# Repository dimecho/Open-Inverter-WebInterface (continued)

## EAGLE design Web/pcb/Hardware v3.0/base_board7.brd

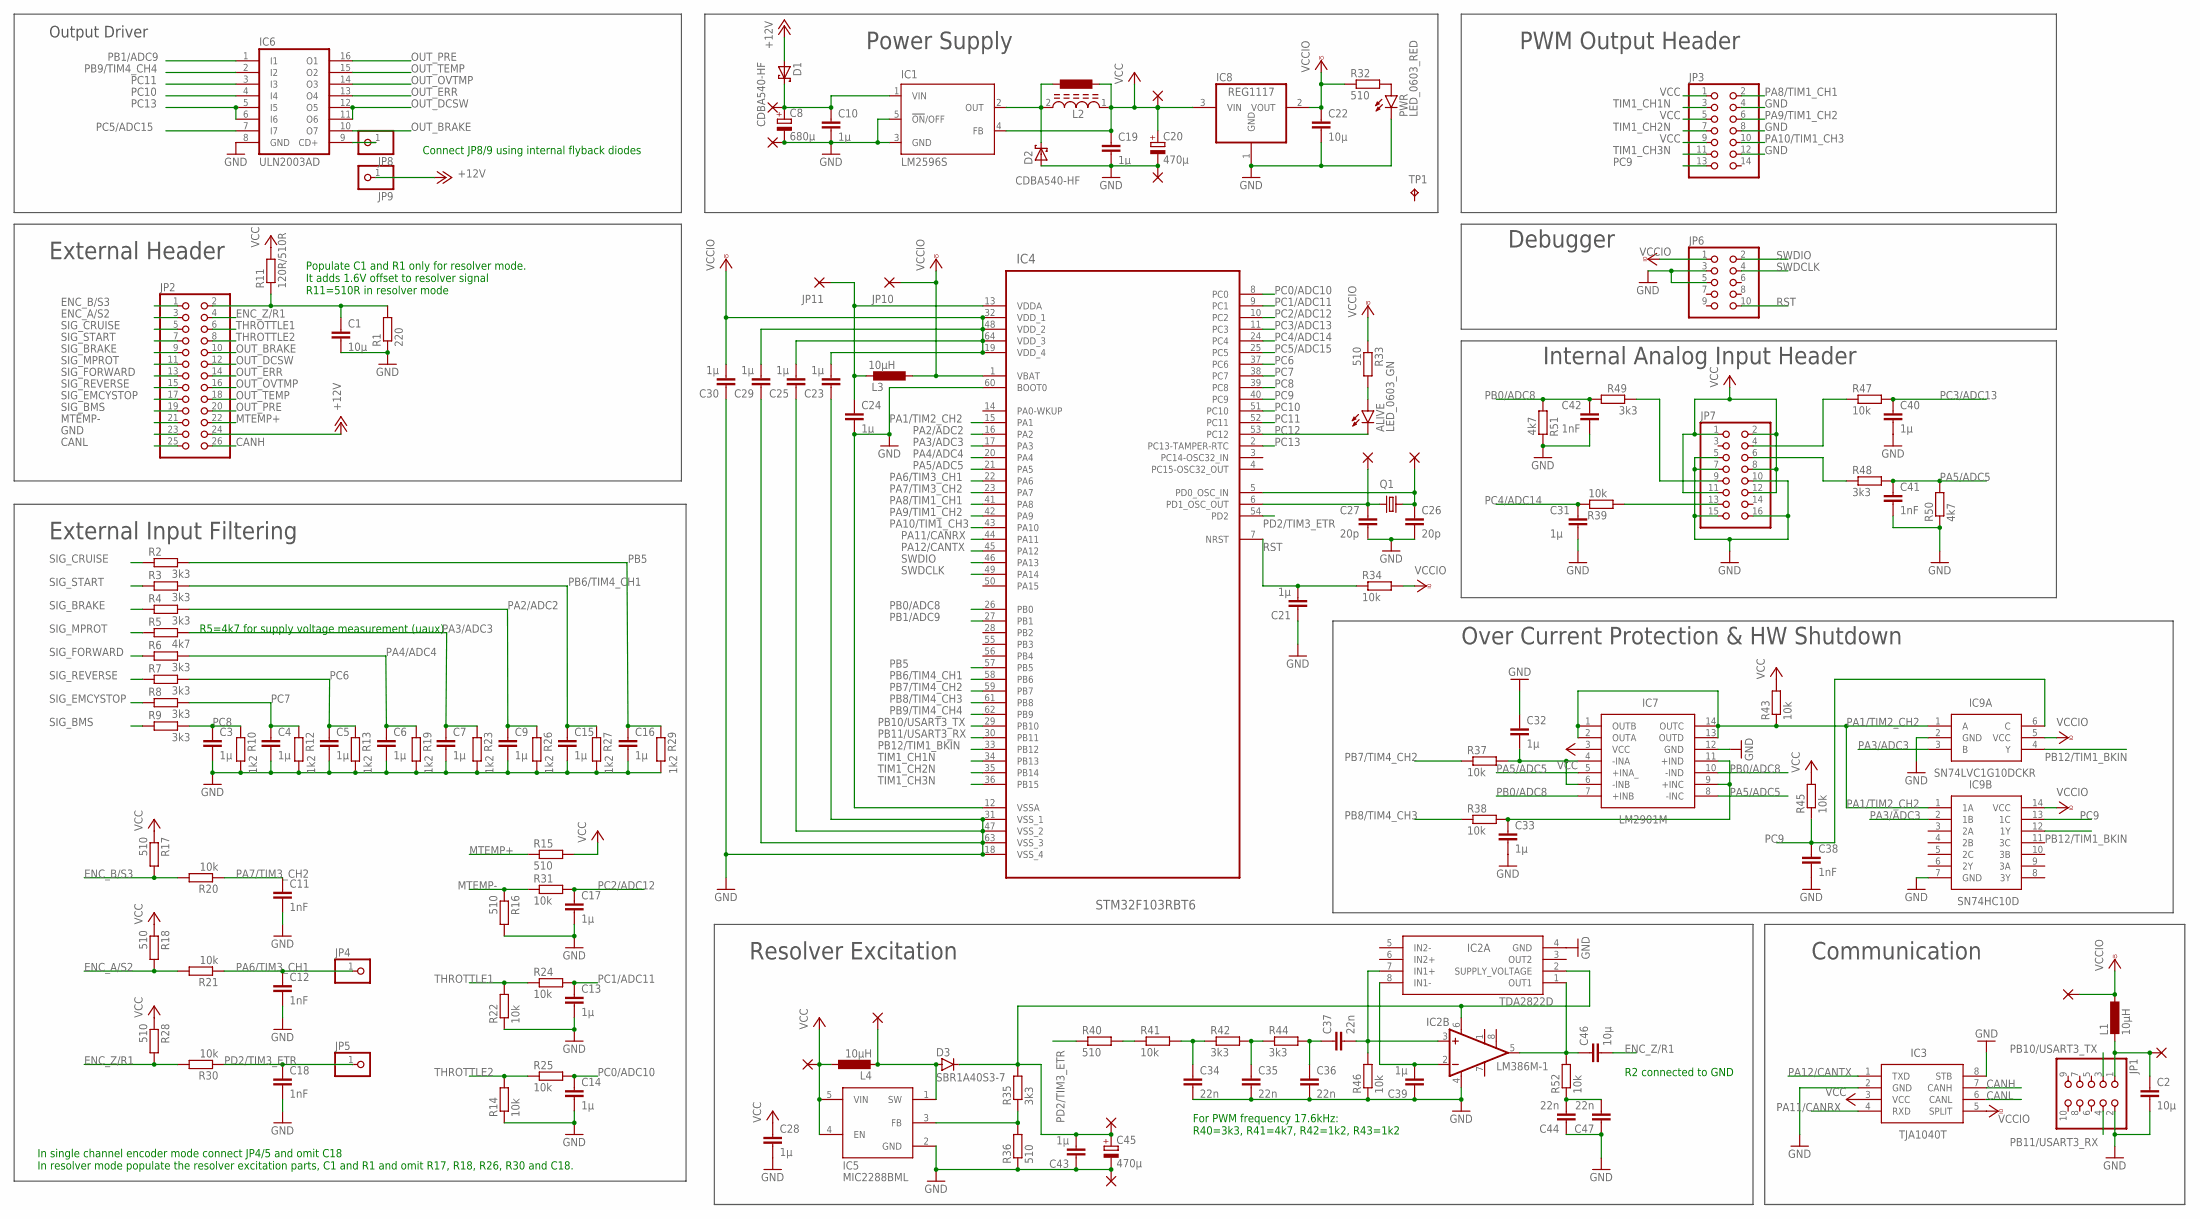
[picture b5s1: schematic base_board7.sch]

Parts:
ALIVE: LED_0603_GN; SML0805
C1, C2, C22, C46: 10µ; C0805K
C3, C4, C5, C6, C7, C9, C10, C13, C14, C15, C16, C17, C19, C21, C23, C24, C25, C28, C29, C30, C31, C32, C33, C39, C40, C43: 1µ; C0603K
C8: 680µ; 153CLV-1014
C11, C12, C18, C38, C41, C42: 1nF; C0603K
C20, C45: 470µ; 153CLV-0605
C26, C27: 20p; C0603K
C34, C35, C36, C37, C44, C47: 22n; C0603K
D1, D2: CDBA540-HF; SMB
D3: SBR1A40S3-7; SOD123
IC1: LM2596S; TO263-5
IC2A: TDA2822D; SOIC127P600X175-8N
IC2B: LM386M-1; SO08
IC3: TJA1040T; SOIC127P600X175-8N
IC4: STM32F103RBT6; QFP50P1200X1200X160-64N
IC5: MIC2288BML; SOT23-5L
IC6: ULN2003AD; SO16
IC7: LM2901M; SOP127P600X180-14N
IC8: REG1117; SOT223
IC9A: SN74LVC1G10DCKR; SOT65P210X110-6N
IC9B: SN74HC10D; SOIC127P600X175-14N
JP1: PINHD-2X5/90; 2X05/90
JP2: PINHD-2X13; 2X13
JP3: PINHD-2X7; 2X07
JP4, JP5, JP8, JP9: PINHD-1X1; 1X01
JP6: PINHD-2X5; 2X05
JP7: PINHD-2X8; 2X08
JP10, JP11: 1,6/0,9
JP12, JP13, JP14, JP15, JP16, JP17: 1,6/0,8
L1, L3, L4: 10µH; L3225M
L2: SRR1260-471K; INDP125125X600N
L5: L-EUTJ3-U1; TJ3-U1
PAD1, PAD2: 1,6/0,9
PAD3, PAD4, PAD5, PAD6: 1,6/0,8
PWR: LED_0603_RED; SML0805
Q1: CSM-7X-DU
R1: 220; R0603
R2, R3, R4, R6, R7, R8, R9, R35, R42, R44, R48, R49: 3k3; R0603
R5, R50, R51: 4k7; R0603
R10, R12, R13, R19, R23, R26, R27, R29: 1k2; R0603
R11: 120R/510R; R0603
R14, R20, R21, R22, R24, R25, R30, R31, R34, R37, R38, R39, R41, R43, R45, R46, R47, R52: 10k; R0603
R15, R16, R17, R18, R28, R32, R33, R36, R40: 510; R0603
TP1: TPB1,27; B1,27

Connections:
+12V: D1.A, JP2.24, JP9.1
CANH: IC3.7 (CANH), JP2.26
CANL: IC3.6 (CANL), JP2.25
ENC_A/S2: JP2.3, R18.2, R21.2
ENC_B/S3: JP2.1, R17.2, R20.2
ENC_Z/R1: C46.2, JP2.4, R28.2, R30.2
GND: C1.2, C2.2, C3.2, C4.2, C5.2, C6.2, C7.2, C8.-, C9.2, C10.2, C11.2, C12.2, C13.2, C14.2, C15.2, C16.2, C17.2, C18.2, C19.2, C20.-, C21.1, C22.2, C23.1, C24.2, C25.1, C26.2, C27.2, C28.2, C29.1, C30.1, C31.2, C32.1, C33.2, C34.2, C35.2, C36.2, C38.2, C39.1, C40.2, C41.2, C42.2, C43.1, C44.1, C45.-, C47.1, D2.A, IC1.3 (GND), IC1.5 (!ON!/OFF), IC2A.4 (GND), IC2B.4 (GND), IC3.2 (GND), IC3.8 (STB), IC4.12 (VSSA), IC4.18 (VSS_4), IC4.31 (VSS_1), IC4.47 (VSS_2), IC4.60 (BOOT0), IC4.63 (VSS_3), IC5.2 (GND), IC6.8 (GND), IC7.12 (GND), IC8.1 (GND), IC9A.2 (GND), IC9B.7 (GND), JP1.2, JP2.23, JP3.4, JP3.8, JP3.12, JP6.3, JP6.5, JP7.5, JP7.7, JP7.10, JP7.15, JP7.16, PAD1.1, PAD3.1, PAD6.1, PWR.C, R1.1, R10.2, R12.2, R13.2, R14.1, R16.2, R19.2, R22.1, R23.2, R26.2, R27.2, R29.2, R36.1, R46.1, R50.1, R51.2
MTEMP+: JP2.22, R15.1
MTEMP-: JP2.21, R16.1, R31.1
unnamed: C1.1, JP2.2, R1.2, R11.1
unnamed: ALIVE.A, R33.2
unnamed: D2.C, IC1.2 (OUT), L2.2, L5.1
unnamed: C8.+, C10.1, D1.C, IC1.1 (VIN), PAD2.1
unnamed: PWR.A, R32.2
unnamed: C27.1, IC4.6 (PD1_OSC_OUT), JP17.1, Q1.1
unnamed: C24.1, IC4.13 (VDDA), JP11.1, L3.1
unnamed: IC6.9 (CD+), JP8.1
unnamed: JP7.9, R49.2
unnamed: JP7.13, R39.1
unnamed: JP7.4, R47.1
unnamed: JP7.6, R48.1
unnamed: C32.2, IC7.4 (-INA), IC7.6 (-INB), R37.2
unnamed: C33.1, IC7.9 (+INC), IC7.11 (+IND), R38.2
unnamed: D3.2 (A), IC5.1 (SW), JP13.1, L4.2
unnamed: IC5.3 (FB), R35.1, R36.2
unnamed: C43.2, C45.+, D3.1 (C), IC2A.2 (SUPPLY_VOLTAGE), IC2B.6 (VS), PAD5.1, R35.2
unnamed: R40.2, R41.1
unnamed: C34.1, R41.2, R42.1
unnamed: C35.1, R42.2, R44.1
unnamed: C36.1, C37.1, R44.2
unnamed: C39.2, IC2A.8 (IN1-), IC2B.2 (-IN)
unnamed: C37.2, IC2A.7 (IN1+), IC2B.3 (+IN), R46.2
unnamed: C44.2, C47.2, R52.1
unnamed: C46.1, IC2A.1 (OUT1), IC2B.5 (OUT), R52.2
unnamed: C2.1, JP1.1, JP15.1, L1.2
unnamed: C26.1, IC4.5 (PD0_OSC_IN), JP16.1, Q1.2
OUT_BRAKE: IC6.10 (O7), JP2.10
OUT_DCSW: IC6.11 (O6), IC6.12 (O5), JP2.12
OUT_ERR: IC6.13 (O4), JP2.14
OUT_OVTMP: IC6.14 (O3), JP2.16
OUT_PRE: IC6.16 (O1), JP2.20
OUT_TEMP: IC6.15 (O2), JP2.18
PA1/TIM2_CH2: IC4.15 (PA1), IC7.1 (OUTB), IC7.2 (OUTA), IC7.13 (OUTD), IC7.14 (OUTC), IC9A.1 (A), IC9B.1 (1A), R43.1
PA2/ADC2: C9.1, IC4.16 (PA2), R4.2, R26.1
PA3/ADC3: C7.1, IC4.17 (PA3), IC9A.3 (B), IC9B.2 (1B), R5.2, R23.1
PA4/ADC4: C6.1, IC4.20 (PA4), R6.2, R19.1
PA5/ADC5: C41.1, IC4.21 (PA5), IC7.5 (+INA_), IC7.8 (-INC), R48.2, R50.2
PA6/TIM3_CH1: C12.1, IC4.22 (PA6), JP4.1, R21.1
PA7/TIM3_CH2: C11.1, IC4.23 (PA7), R20.1
PA8/TIM1_CH1: IC4.41 (PA8), JP3.2
PA9/TIM1_CH2: IC4.42 (PA9), JP3.6
PA10/TIM1_CH3: IC4.43 (PA10), JP3.10
PA11/CANRX: IC3.4 (RXD), IC4.44 (PA11)
PA12/CANTX: IC3.1 (TXD), IC4.45 (PA12)
PB0/ADC8: C42.1, IC4.26 (PB0), IC7.7 (+INB), IC7.10 (-IND), R49.1, R51.1
PB1/ADC9: IC4.27 (PB1), IC6.1 (I1)
PB5: C16.1, IC4.57 (PB5), R2.2, R29.1
PB6/TIM4_CH1: C15.1, IC4.58 (PB6), R3.2, R27.1
PB7/TIM4_CH2: IC4.59 (PB7), R37.1
PB8/TIM4_CH3: IC4.61 (PB8), R38.1
PB9/TIM4_CH4: IC4.62 (PB9), IC6.2 (I2)
PB10/USART3_TX: IC4.29 (PB10), JP1.3
PB11/USART3_RX: IC4.30 (PB11), JP1.4
PB12/TIM1_BKIN: IC4.33 (PB12), IC9A.4 (Y), IC9B.12 (1Y)
PC0/ADC10: C14.1, IC4.8 (PC0), R25.2
PC1/ADC11: C13.1, IC4.9 (PC1), R24.2
PC2/ADC12: C17.1, IC4.10 (PC2), R31.2
PC3/ADC13: C40.1, IC4.11 (PC3), R47.2
PC4/ADC14: C31.1, IC4.24 (PC4), R39.2
PC5/ADC15: IC4.25 (PC5), IC6.7 (I7)
PC6: C5.1, IC4.37 (PC6), R7.2, R13.1
PC7: C4.1, IC4.38 (PC7), R8.2, R12.1
PC8: C3.1, IC4.39 (PC8), R9.2, R10.1
PC9: C38.1, IC4.40 (PC9), IC9A.6 (C), IC9B.13 (1C), JP3.13, R45.1
PC10: IC4.51 (PC10), IC6.4 (I4)
PC11: IC4.52 (PC11), IC6.3 (I3)
PC12: ALIVE.C, IC4.53 (PC12)
PC13: IC4.2 (PC13-TAMPER-RTC), IC6.5 (I5), IC6.6 (I6)
PD2/TIM3_ETR: C18.1, IC4.54 (PD2), JP5.1, R30.1, R40.1
RST: C21.2, IC4.7 (NRST), JP6.10, R34.1
SIG_BMS: JP2.19, R9.1
SIG_BRAKE: JP2.9, R4.1
SIG_CRUISE: JP2.5, R2.1
SIG_EMCYSTOP: JP2.17, R8.1
SIG_FORWARD: JP2.13, R6.1
SIG_MPROT: JP2.11, R5.1
SIG_REVERSE: JP2.15, R7.1
SIG_START: JP2.7, R3.1
SWDCLK: IC4.49 (PA14), JP6.4
SWDIO: IC4.46 (PA13), JP6.2
THROTTLE1: JP2.6, R22.2, R24.1
THROTTLE2: JP2.8, R14.2, R25.1
TIM1_CH1N: IC4.34 (PB13), JP3.3
TIM1_CH2N: IC4.35 (PB14), JP3.7
TIM1_CH3N: IC4.36 (PB15), JP3.11
VCC: C19.1, C20.+, C28.1, IC1.4 (FB), IC3.3 (VCC), IC5.4 (EN), IC5.5 (VIN), IC7.3 (VCC), IC8.3 (VIN), JP3.1, JP3.5, JP3.9, JP7.1, JP7.2, JP7.8, JP7.11, JP7.12, JP12.1, L2.1, L4.1, L5.2, PAD4.1, R11.2, R15.2, R17.1, R18.1, R28.1, R43.2, R45.2
VCCIO: C22.1, C23.2, C25.2, C29.2, C30.2, IC3.5 (SPLIT), IC4.1 (VBAT), IC4.19 (VDD_4), IC4.32 (VDD_1), IC4.48 (VDD_2), IC4.64 (VDD_3), IC8.2 (VOUT), IC9A.5 (VCC), IC9B.14 (VCC), JP6.1, JP10.1, JP14.1, L1.1, L3.2, R32.1, R33.1, R34.2

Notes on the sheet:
Output Driver
Populate C1 and R1 only for resolver mode. It adds 1.6V offset to resolver signal R11=510R in resolver mode
Connect JP8/9 using internal flyback diodes
External Header
External Input Filtering
R5=4k7 for supply voltage measurement (uaux)
In single channel encoder mode connect JP4/5 and omit C18 In resolver mode populate the resolver excitation parts, C1 and R1 and omit R17, R18, R26, R30 and C18.
PWM Output Header
Power Supply
Internal Analog Input Header
Over Current Protection & HW Shutdown
Resolver Excitation
For PWM frequency 17.6kHz: R40=3k3, R41=4k7, R42=1k2, R43=1k2
R2 connected to GND
Communication
Debugger

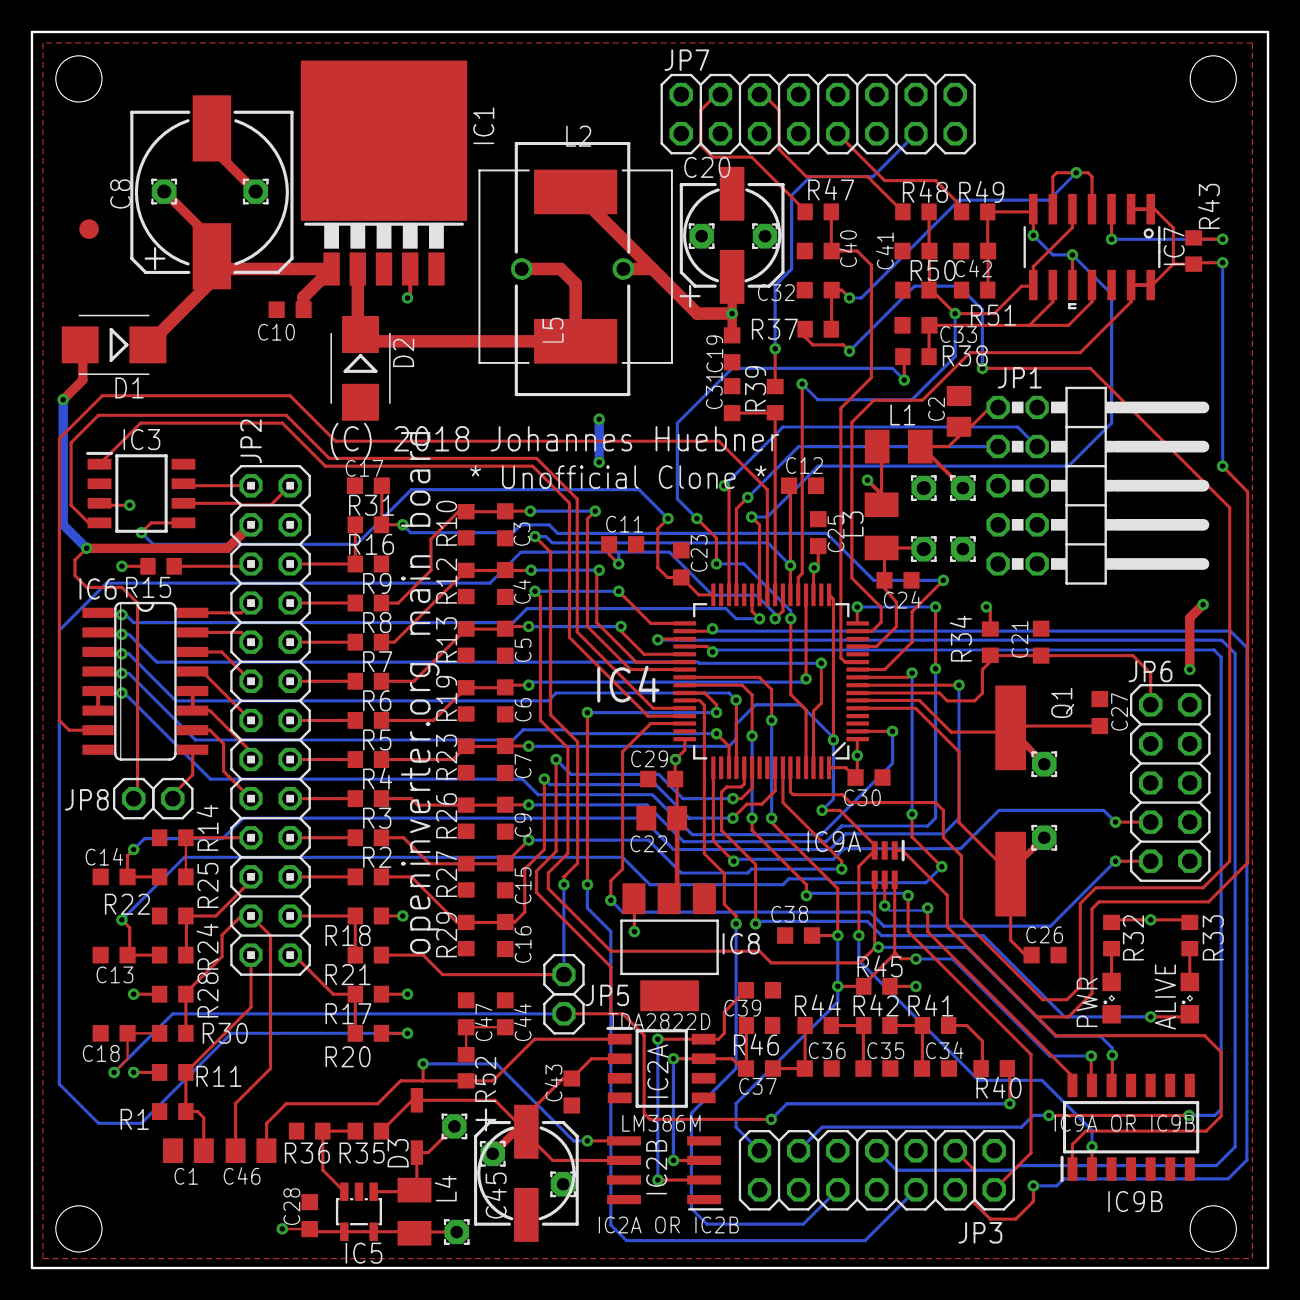
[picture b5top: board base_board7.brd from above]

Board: 2 copper layers, 80.3 x 80.3 mm, 145 parts (0 on the bottom side), 97 nets.

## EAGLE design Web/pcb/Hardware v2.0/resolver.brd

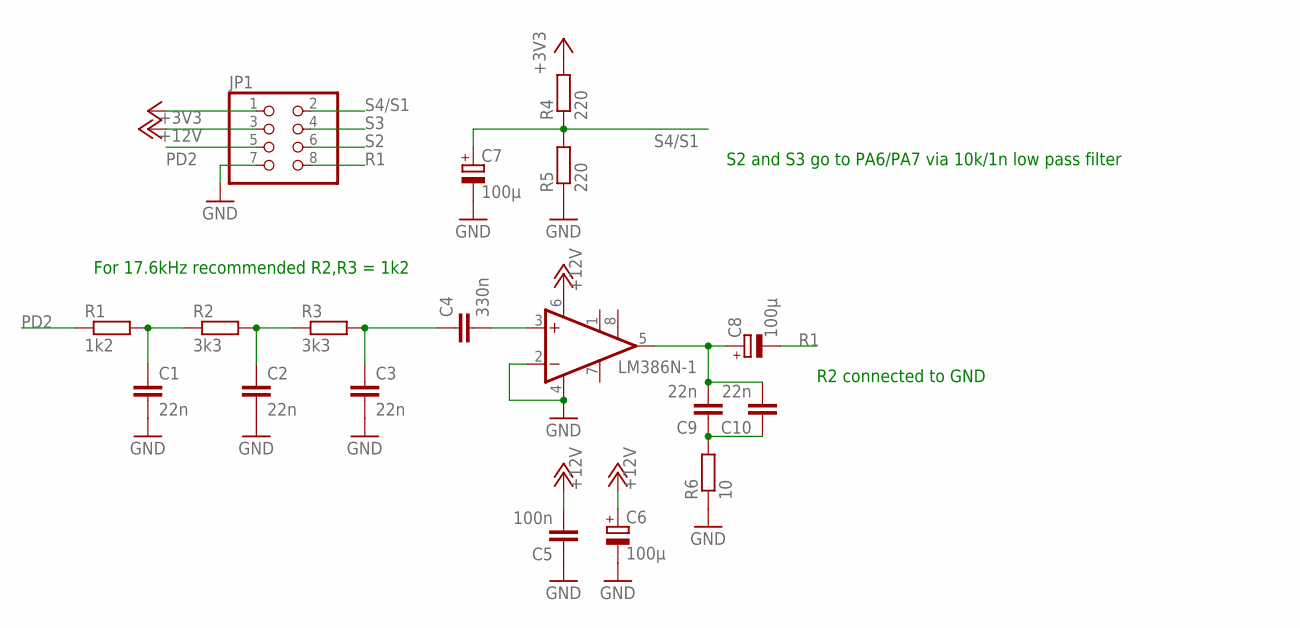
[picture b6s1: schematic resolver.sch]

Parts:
C1, C2, C3, C9, C10: 22n; C050-024X044
C4: 330n; C025-024X044
C5: 100n; C025-024X044
C6, C7, C8: 100µ; E2,5-6E
IC1: LM386N-1; DIL08
JP1: PINHD-2X4; 2X04
R1: 1k2; 0204V
R2, R3: 3k3; 0204V
R4: 220; 0207/10
R5: 220; 0204V
R6: 10; 0204V

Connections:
+3V3: JP1.1, R4.2
+12V: C5.2, C6.+, IC1.6 (VS), JP1.3
GND: C1.2, C2.2, C3.2, C5.1, C6.-, C7.-, IC1.2 (-IN), IC1.4 (GND), JP1.7, R5.1, R6.1
unnamed: C8.+, C9.2, C10.2, IC1.5 (OUT)
unnamed: C3.1, C4.1, R3.2
unnamed: C4.2, IC1.3 (+IN)
unnamed: C1.1, R1.2, R2.1
unnamed: C2.1, R2.2, R3.1
unnamed: C9.1, C10.1, R6.2
PD2: JP1.5, R1.1
R1: C8.-, JP1.8
S2: JP1.6
S3: JP1.4
S4/S1: C7.+, JP1.2, R4.1, R5.2

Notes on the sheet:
S2 and S3 go to PA6/PA7 via 10k/1n low pass filter
R2 connected to GND
For 17.6kHz recommended R2,R3 = 1k2

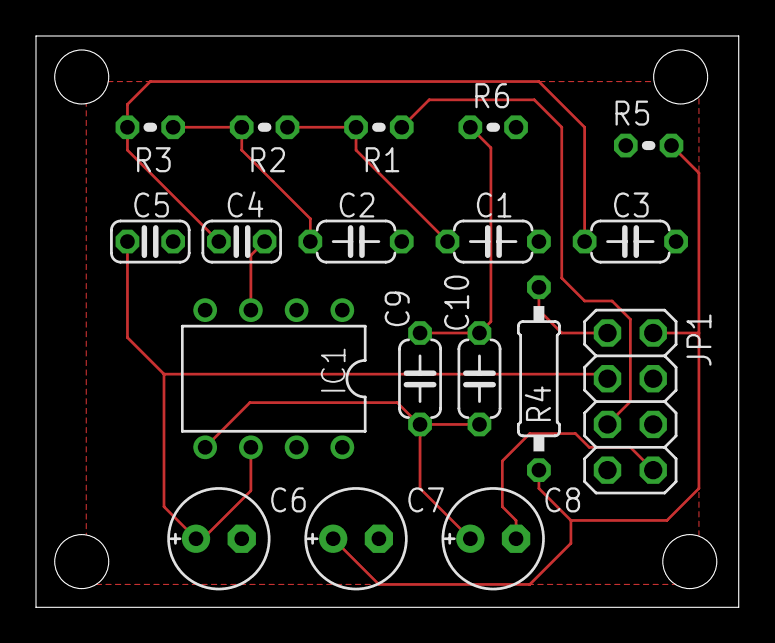
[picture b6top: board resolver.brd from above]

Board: 2 copper layers, 39.0 x 31.7 mm, 18 parts (0 on the bottom side), 12 nets.

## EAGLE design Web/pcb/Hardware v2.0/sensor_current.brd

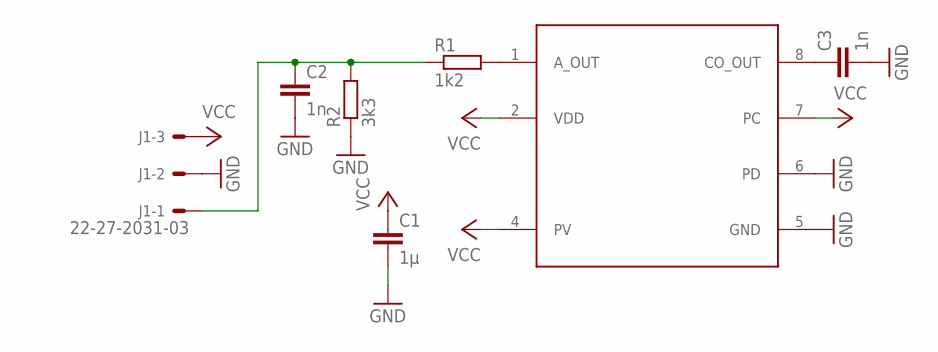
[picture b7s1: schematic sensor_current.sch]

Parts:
C1: 1µ; C025-024X044
C2, C3: 1n; C025-024X044
IC1: MLX91205; SO-08
J1: 22-27-2031-03; 6410-03
R1: 1k2; 0204V
R2: 3k3; 0204V

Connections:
GND: C1.2, C2.2, C3.2, IC1.5 (GND), IC1.6 (PD), J1.2, R2.1
unnamed: IC1.1 (A_OUT), R1.2
unnamed: C3.1, IC1.8 (CO_OUT)
unnamed: C2.1, J1.1, R1.1, R2.2
VCC: C1.1, IC1.2 (VDD), IC1.4 (PV), IC1.7 (PC), J1.3

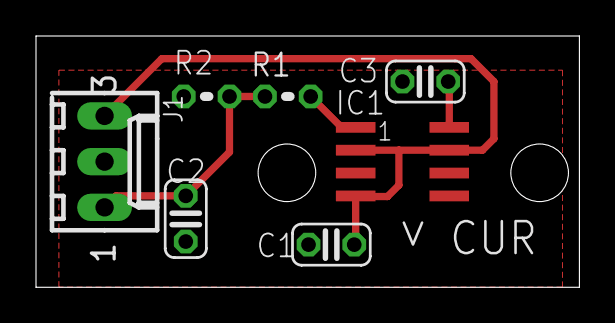
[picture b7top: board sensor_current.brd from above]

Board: 2 copper layers, 30.2 x 14.0 mm, 7 parts (0 on the bottom side), 5 nets.

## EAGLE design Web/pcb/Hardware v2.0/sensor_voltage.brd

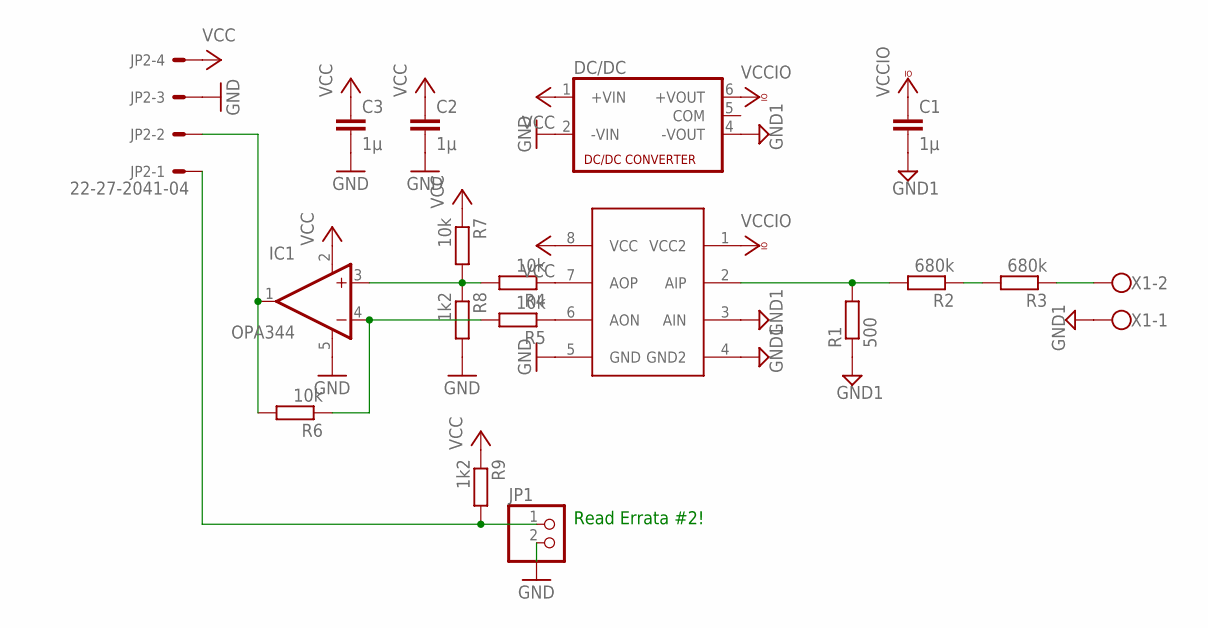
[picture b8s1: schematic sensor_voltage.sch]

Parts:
C1, C2, C3: 1µ; C025-024X044
DC/DC: MEV3; NMA
IC1: OPA344; SOT23-5
IC2: SI8920; DIP8
JP1: PINHD-1X2; 1X02
JP2: 22-27-2041-04; 6410-04
R1: 500; 0207/10
R2, R3: 680k; 0207/10
R4, R5, R6, R7: 10k; 0207/10
R8, R9: 1k2; 0207/10
X1: W237-102

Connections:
GND: C2.2, C3.2, DC/DC.2 (-VIN), IC1.5 (V+), IC2.5 (GND), JP1.2, JP2.3, R8.2
GND1: C1.2, DC/DC.4 (-VOUT), IC2.3 (AIN), IC2.4 (GND2), R1.1, X1.1
unnamed: IC2.2 (AIP), R1.2, R2.2
unnamed: R2.1, R3.2
unnamed: R3.1, X1.2
unnamed: IC2.7 (AOP), R4.1
unnamed: IC2.6 (AON), R5.1
unnamed: IC1.1 (OUT), JP2.2, R6.2
unnamed: IC1.4 (-IN), R5.2, R6.1
unnamed: IC1.3 (+IN), R4.2, R7.2, R8.1
unnamed: JP1.1, JP2.1, R9.2
VCC: C2.1, C3.1, DC/DC.1 (+VIN), IC1.2 (V-), IC2.8 (VCC), JP2.4, R7.1, R9.1
VCCIO: C1.1, DC/DC.6 (+VOUT), IC2.1 (VCC2)

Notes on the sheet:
Read Errata #2!

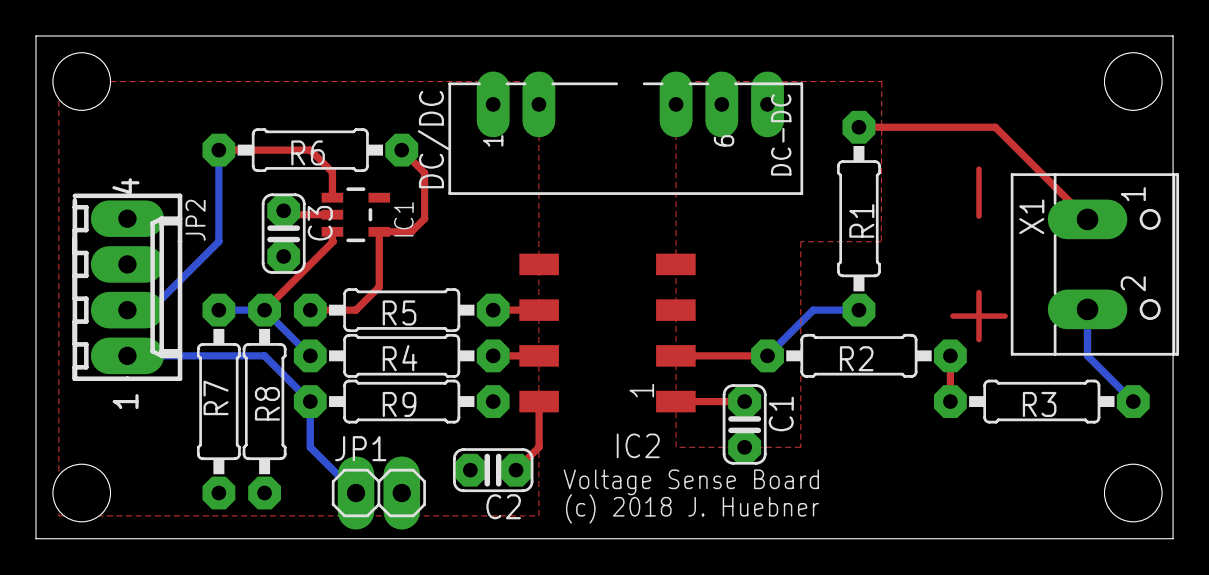
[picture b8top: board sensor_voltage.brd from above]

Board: 2 copper layers, 63.2 x 27.9 mm, 18 parts (0 on the bottom side), 13 nets.

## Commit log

2016-05-16 readme
2016-05-16 installer fix
2016-05-18 added encoder builder with Inkscape
2016-05-19 inkscape fix
2016-05-20 small GUI fixes
2016-05-20 screenshot
2016-05-22 converted to Swift2.0
2016-05-22 ready
2016-05-25 added eagle helper
2016-05-27 firmware helper
2016-05-31 added graph and defaults
2016-05-31 graph
2016-06-21 added IGBT test procedure
2016-06-21 added Olimex debugger driver
2016-06-21 added bootloader flash
2016-06-23 fixed bootloader flash
2016-07-27 improvements
2016-07-28 component list
2016-07-30 fixed wiring diagram
2016-08-02 ported to Windows
2016-08-06 added refresh and tips
2016-08-07 OS X added support for more USB drivers
2016-08-09 added encoder wheel SVG to 3D printing
2016-08-14 attiny avr flash
2016-08-17 driver fix for Windows
2016-08-22 less os dependent
2016-08-28 lots of updates win & mac
2016-08-29 graph improvements
2016-09-01 updates for windows
2016-09-05 powershell fix
2016-09-10 added motor database list
2016-09-10 parameter upload fix
2016-09-18 graphs
2016-09-19 encoder tune-up
2016-09-21 manual control correction
2016-10-04 motor db
2016-10-16 gui updates
2016-10-22 lots of updates
2016-10-28 pcb corrections
2016-11-06 linux updates
2016-11-08 corrections
2016-12-16 tuning web
2016-12-21 added 3d model
2016-12-22 more 3d
2016-12-24 fixes for linux
2016-12-28 tunning fixes
2016-12-29 Xcode update 8.2
2017-01-07 windows fix
2017-01-15 fixed incorrect float value read
2017-01-15 more float value corrections
2017-01-17 menu updates
2017-01-27 library updates
2017-02-09 some updates
2017-02-14 added encoder info
2017-02-15 fix inkscape encoder
2017-02-21 added stm32 pin description
2017-02-23 Eagle updates
2017-03-01 added fancybox and stuff
2017-03-02 added PWM graphs
2017-03-04 added AC-35 motor
2017-03-17 cleaner 3rd party software checks
2017-03-26 eagle download correction
2017-03-29 added raspberryPi dashboard ui
2017-04-02 more pi + windows fix
2017-04-19 added DesignSparkPCB for mac
2017-04-21 a few fixes
2017-05-07 added uninstaller
2017-05-12 converted updater to php
2017-05-16 removed dio() and phpserial dependencies
2017-05-17 corrections for macos
2017-05-18 more fixes for macos
2017-05-19 build 33
2017-05-22 more macos fixes
2017-05-26 fixes
2017-06-17 optimized
2017-06-20 added j-link adapter
2017-09-06 update to bootstrap v4
2017-09-24 bootstrap4 fix
2017-09-24 macOS correction
2017-10-15 fixed number check for floats
2017-10-16 fixed windows space in path
2017-10-23 added CAN mapping GUI
2017-10-25 added category icons
2017-10-26 more updates
2017-10-26 more CAN stuff
2017-10-27 even more CAN
2017-10-28 bootloader flash can now be hex
2017-11-07 fix for windows
2017-11-12 fixed svg icons
2017-12-25 optimized for mobile
2017-12-25 more mobile fixing
2017-12-27 raspberry pi fix
2017-12-28 faster load speed
2017-12-29 pi fixes
2017-12-29 better mobile graphs
2017-12-30 graph fix
2018-01-08 serial improvement
2018-02-07 graph updates
2018-02-11 fixed DesignSpark PCPB for mac
2018-02-15 added raspberrypi
2018-02-17 pi zero fixed
2018-03-12 esp8266 updates
2018-03-16 pin correction
2018-03-25 more esp
2018-03-26 added esp nvram settings
2018-03-29 esp fixed firmware flash
2018-03-31 readme updates
2018-04-02 attiny13 better doco
2018-04-03 esp updates
2018-04-16 mac 10.13 driver update
2018-09-18 st-link tutorial
2018-10-29 php serial fixes
2018-10-30 windows fixes
2018-11-06 xcode updates
2018-11-10 serial updates
2018-11-12 serial fixes
2018-11-13 mac fixes
2018-11-17 many fixes
2018-11-26 cleanup
2018-12-02 v3 bom
2018-12-04 v3 bom updates
2018-12-06 esp build
2018-12-19 stlink cleanup
2018-12-21 stlink updates
2018-12-28 many updates
2019-01-02 diagram updates and various improvements.
2019-01-05 added CAN info and temp detection
2019-01-18 software updates
2019-01-19 swd over esp progress
2019-01-26 optimized icons
2019-02-03 some pcb optimizations
2019-02-07 board test confirmed
2019-02-21 ui updates
2019-03-24 Fix Windows multi COM
2019-05-04 added csv export for graph
2019-07-18 canbus fix
2019-07-19 more canbus work
2019-07-24 can updates
2019-07-25 dfu firmware fixes
2019-08-21 a few small updates
2019-09-10 windows bug fix
2019-09-11 esp fix
2019-10-04 fix for sin32_foc
2019-10-05 added udcnom calculator
2019-10-06 improved charts
2019-10-25 build 40
2019-11-20 syncofs calculator
2020-01-09 better scripts
2020-01-21 fixes and updates
2020-02-07 fixed serial for linux
2020-04-25 code restructured
2020-05-24 esp8266 to async webserver
2020-05-26 migrated spiffs to littlefs
2020-05-30 fixed eeprom init bug
2020-05-31 added https/ssl code
2020-09-11 optimizations and updates
2020-09-15 added syncof tuner gui and flash fix
2020-09-18 many fixes esp and mac
2020-10-05 dev updates
2020-10-05 dev win fix
2020-11-15 better status refresh
2020-11-25 swd over esp8266
2020-11-25 buffer fix
2020-11-26 more buffer tweak
2020-11-27 uart + swd work together
2021-12-12 updates - bootstrap, chart.js, swd
